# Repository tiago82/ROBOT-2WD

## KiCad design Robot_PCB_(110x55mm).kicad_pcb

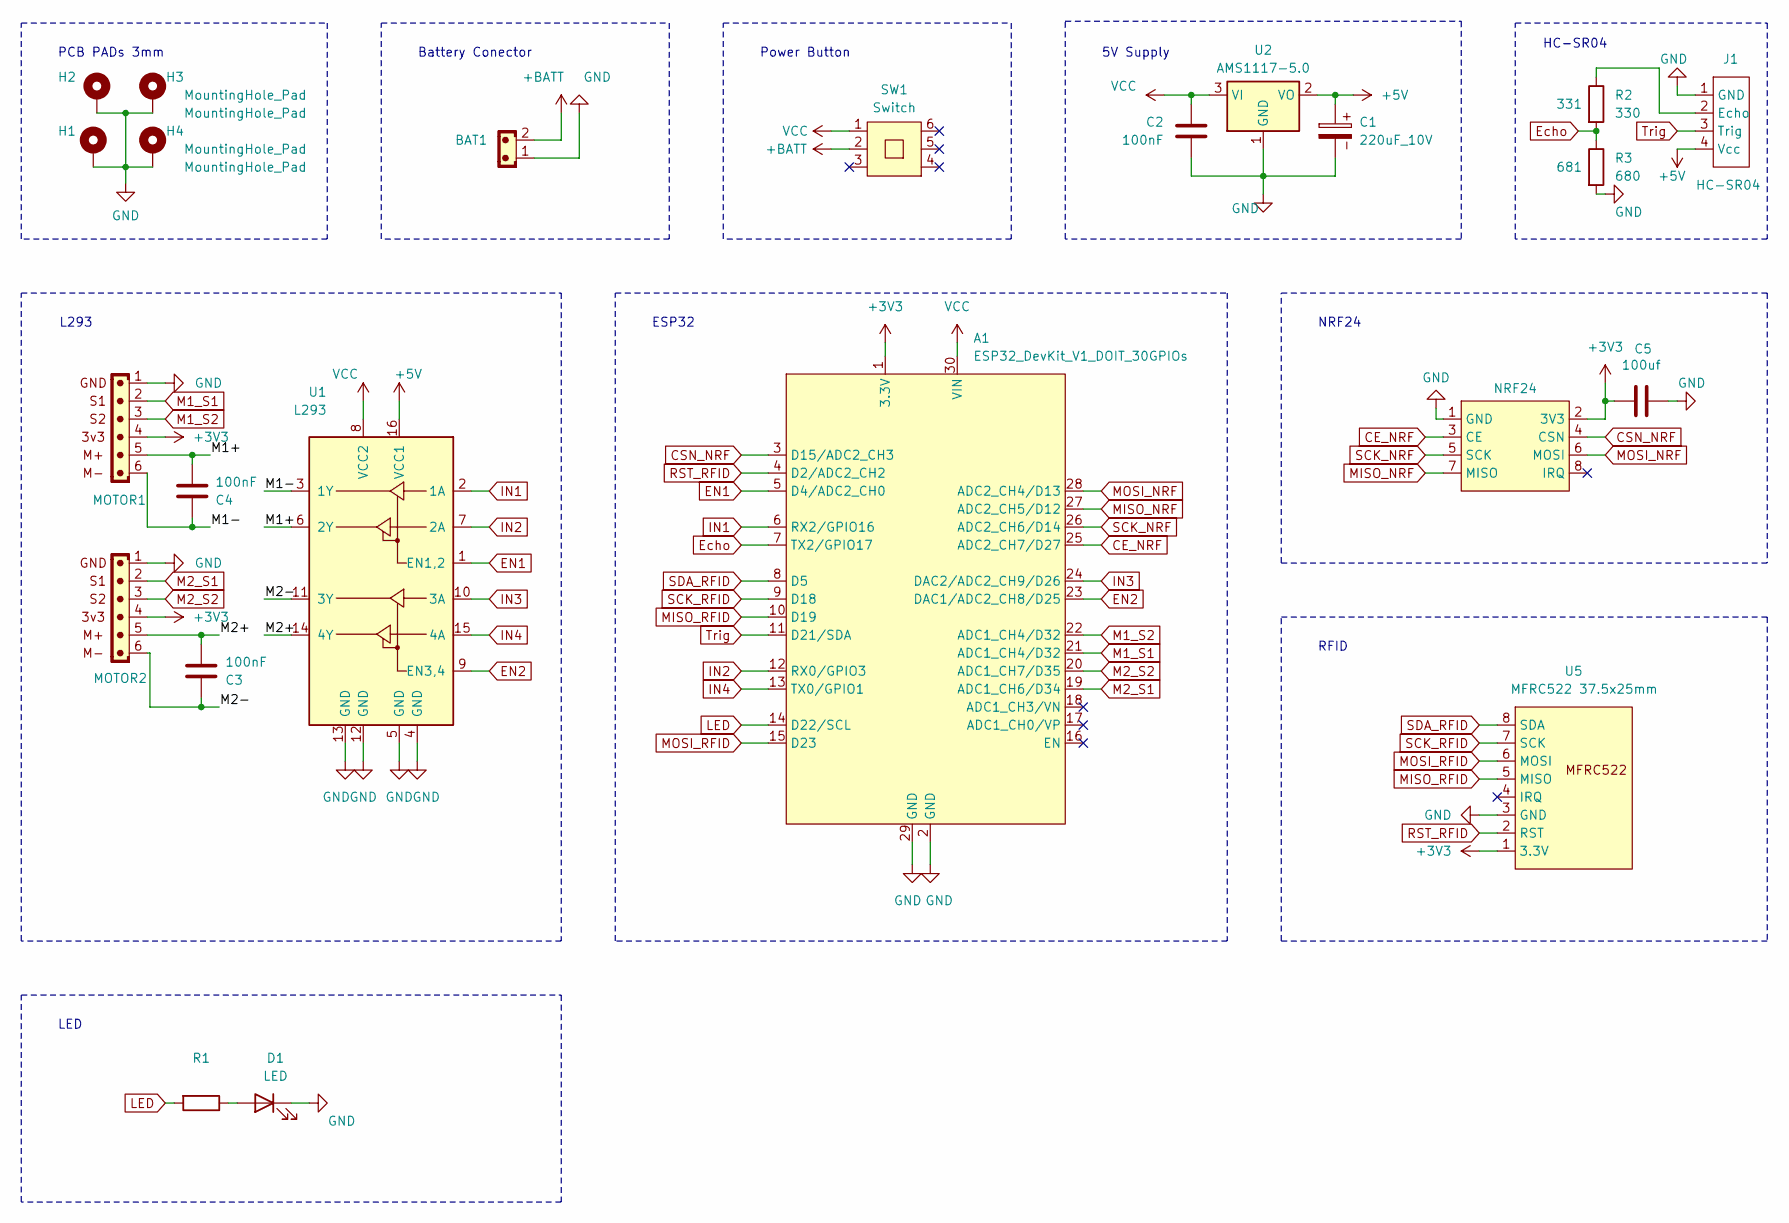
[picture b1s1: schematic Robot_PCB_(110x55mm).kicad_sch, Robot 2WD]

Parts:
A1: ESP32_DevKit_V1_DOIT_30GPIOs; DOIT_ESP32_DEVKIT_30Pins
BAT1: JST_02; JST_EH_B2B-EH-A_1x02_P2.50mm_Vertical
C1: 220uF_10V; CP_Radial_D6.3mm_P2.50mm
C2, C3, C4: 100nF; C_0805_2012Metric_Pad1.18x1.45mm_HandSolder
C5: 100uf; C_0805_2012Metric_Pad1.18x1.45mm_HandSolder
D1: LED; LED_D3.0mm_Clear
H1, H2, H3, H4: MountingHole_Pad; MountingHole_3.2mm_M3_DIN965_Pad
J1: HC-SR04
MOTOR1, MOTOR2: MOTOR ENC JST_06 (PH2.0) Horizontal; Encoder Socket
NRF24: NRF24; NRF24_SOCKET
R1: R_0805_2012Metric_Pad1.20x1.40mm_HandSolder
R2: 330; R_0805_2012Metric_Pad1.20x1.40mm_HandSolder
R3: 680; R_0805_2012Metric_Pad1.20x1.40mm_HandSolder
SW1: Switch; Push Button Switch 7mm
U1: L293; DIP-16_W7.62mm_IC_Socket
U2: AMS1117-5.0; SOT-223-3_TabPin2
U5: MFRC522 37.5x25mm

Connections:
+3V3: A1.1 (3.3V), C5.1, MOTOR1.4, MOTOR2.4, NRF24.2 (3V3), U5.1 (3.3V)
+5V: C1.1, J1.4 (Vcc), U1.16 (VCC1), U2.2 (VO)
+BATT: BAT1.2, SW1.2
/M1+: C4.2, MOTOR1.5, U1.6 (2Y)
/M1-: C4.1, MOTOR1.6, U1.3 (1Y)
/M2+: C3.2, MOTOR2.5, U1.14 (4Y)
/M2-: C3.1, MOTOR2.6, U1.11 (3Y)
CE_NRF: A1.25 (ADC2_CH7/D27), NRF24.3 (CE)
CSN_NRF: A1.3 (D15/ADC2_CH3), NRF24.4 (CSN)
EN1: A1.5 (D4/ADC2_CH0), U1.1 (EN1,2)
EN2: A1.23 (DAC1/ADC2_CH8/D25), U1.9 (EN3,4)
Echo: A1.7 (TX2/GPIO17), R2.2, R3.1
GND: A1.2 (GND), A1.29 (GND), BAT1.1, C1.2, C2.1, C5.2, D1.1 (K), H1.1, H2.1, H3.1, H4.1, J1.1 (GND), MOTOR1.1, MOTOR2.1, NRF24.1 (GND), R3.2, U1.4 (GND), U1.5 (GND), U1.12 (GND), U1.13 (GND), U2.1 (GND), U5.3 (GND)
IN1: A1.6 (RX2/GPIO16), U1.2 (1A)
IN2: A1.12 (RX0/GPIO3), U1.7 (2A)
IN3: A1.24 (DAC2/ADC2_CH9/D26), U1.10 (3A)
IN4: A1.13 (TX0/GPIO1), U1.15 (4A)
LED: A1.14 (D22/SCL), R1.2
M1_S1: A1.21 (ADC1_CH4/D32), MOTOR1.2
M1_S2: A1.22 (ADC1_CH4/D32), MOTOR1.3
M2_S1: A1.19 (ADC1_CH6/D34), MOTOR2.2
M2_S2: A1.20 (ADC1_CH7/D35), MOTOR2.3
MISO_NRF: A1.27 (ADC2_CH5/D12), NRF24.7 (MISO)
MISO_RFID: A1.10 (D19), U5.5 (MISO)
MOSI_NRF: A1.28 (ADC2_CH4/D13), NRF24.6 (MOSI)
MOSI_RFID: A1.15 (D23), U5.6 (MOSI)
unnamed: D1.2 (A), R1.1
unnamed: J1.2 (Echo), R2.1
RST_RFID: A1.4 (D2/ADC2_CH2), U5.2 (RST)
SCK_NRF: A1.26 (ADC2_CH6/D14), NRF24.5 (SCK)
SCK_RFID: A1.9 (D18), U5.7 (SCK)
SDA_RFID: A1.8 (D5), U5.8 (SDA)
Trig: A1.11 (D21/SDA), J1.3 (Trig)
VCC: A1.30 (VIN), C2.2, SW1.1, U1.8 (VCC2), U2.3 (VI)

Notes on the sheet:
NRF24
LED
HC-SR04
Battery Conector
PCB PADs 3mm
Power Button
5V Supply
RFID
ESP32
L293

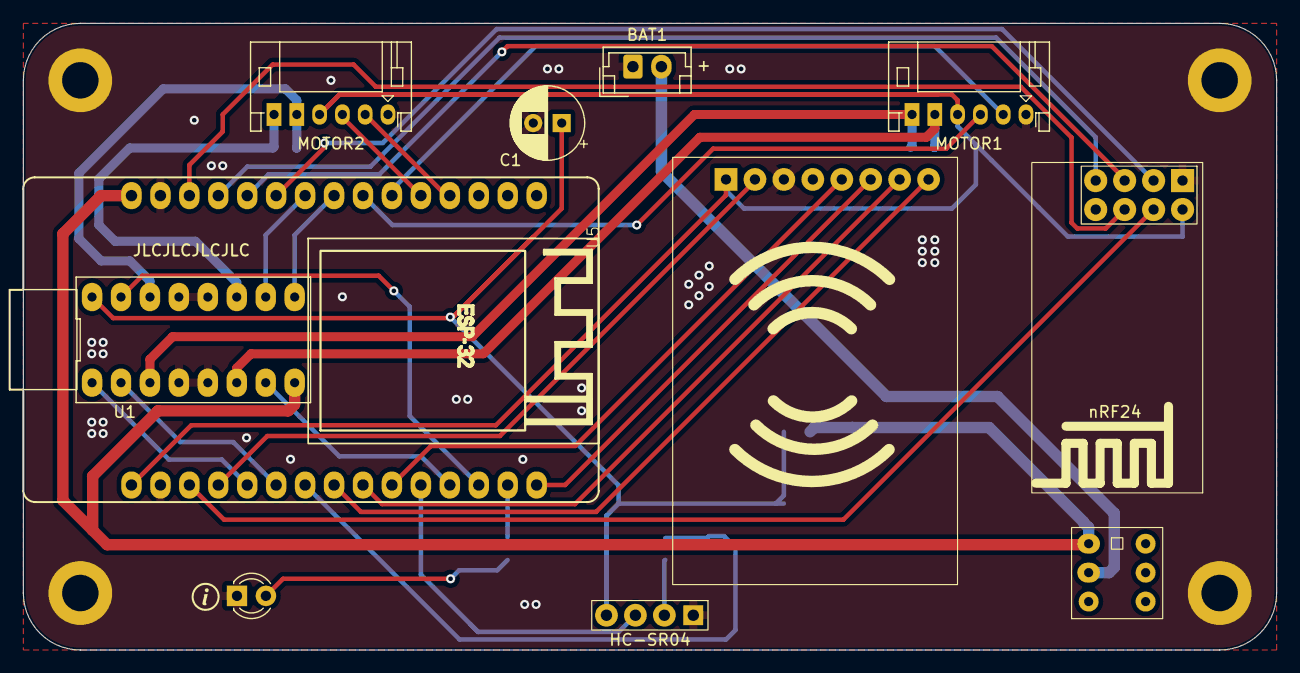
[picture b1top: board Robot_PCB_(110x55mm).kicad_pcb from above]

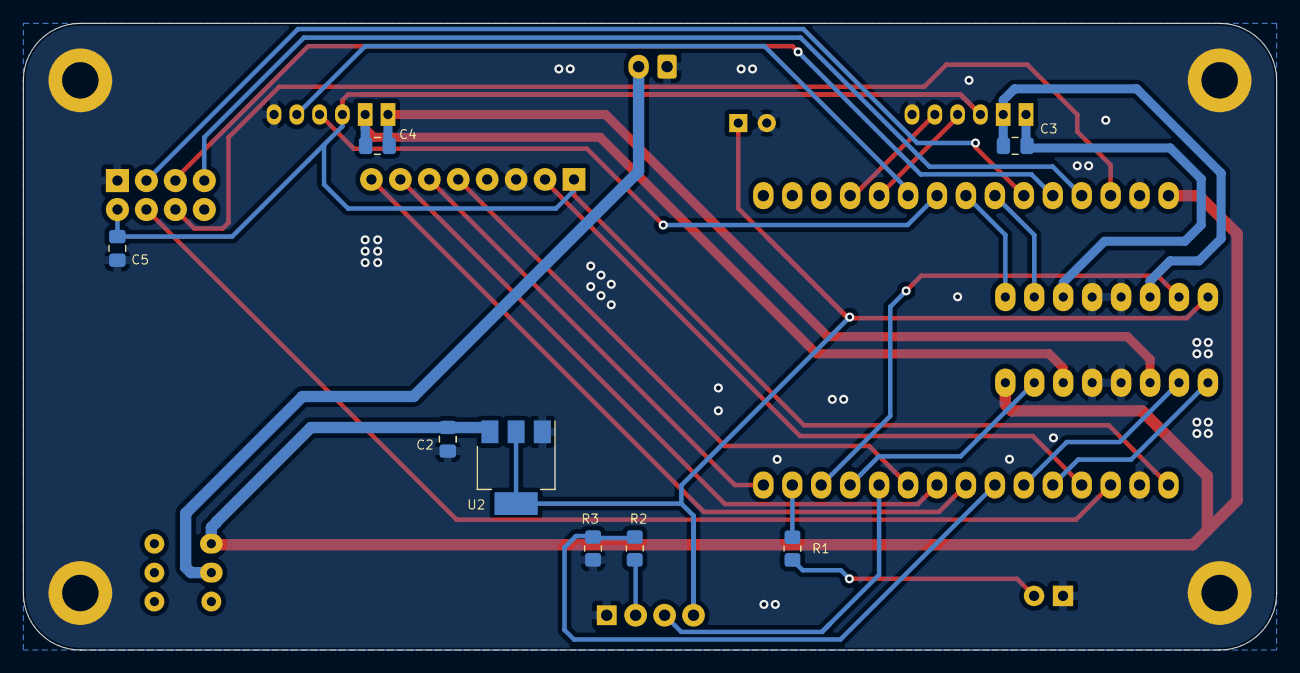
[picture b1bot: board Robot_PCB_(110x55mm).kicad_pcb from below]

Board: 2 copper layers, 110.0 x 55.0 mm, 23 parts (8 on the bottom side), 34 nets.

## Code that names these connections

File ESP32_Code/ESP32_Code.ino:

//============== PCB Pinout ==============
#define RST_RFID 2
#define SDA_RFID 5
#define SCK_RFID 18
#define MISO_RFID 19
#define MOSI_RFID 23

#define CSN_NRF 15
#define MOSI_NRF 13
#define MISO_NRF 12
#define SCK_NRF 14
#define CE_NRF 27

#define EN1 4
#define EN2 25
#define IN1 16
#define IN2 3
#define IN3 26
#define IN4 1

#define M1_S1 32
#define M1_S2 33
#define M2_S1 34
#define M2_S2 35

#define TRIG_PIN 21
#define ECHO_PIN 17

#define BUZZER_PIN 22
//========================================





void setup()
{

}

void loop()
{

}

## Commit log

2023-10-20 Update 17:35
2023-10-20 Update Robot_PCB_(110x55mm).kicad_sch
    Update
2023-10-21 Update 11:14 - 21/10/23
